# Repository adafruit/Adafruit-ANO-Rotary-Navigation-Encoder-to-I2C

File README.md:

## Adafruit ANO Rotary Navigation Encoder to I2C Stemma QT Adapter PCB

<a href="http://www.adafruit.com/products/5740"><br/>
Click here to purchase one from the Adafruit shop</a>

PCB files for the Adafruit ANO Rotary Navigation Encoder to I2C Stemma QT Adapter. 

Format is EagleCAD schematic and board layout
* https://www.adafruit.com/product/5740

### Description

The ANO rotary encoder wheel is a funky user interface element, reminiscent of the original clicking scroll wheel interface on the first iPods. It's a nifty kit, but the pin-out is a little odd - and there's a ton of pins needed to connect to the rotary encoder and 5 button switches.

This Stemma QT breakout makes all that frustration go away - solder in the ANO Directional Navigation and Scroll Wheel Rotary Encoder (not included). The onboard microcontroller is programmed with our seesaw firmware and will track all pulses and pins for you and then save the incremental value for querying at any time over I2C. Plug it in with a Stemma QT cable for instant rotary goodness, with any kind of microcontroller from an Arduino UNO up to a Raspberry Pi to one of our QT Py's.

You can use our Arduino library to control and read data with any compatible microcontroller. We also have CircuitPython/Python code for use with computers or single-board Linux boards.

Power with 3 to 5V DC, and then use 3 or 5V logic I2C data. The INT pin can be configured to pulse low whenever rotation or push-buttoning is detected so you do not have to spam-read the I2C port to detect motion. It's also easy to add this breakout to a breadboard - with six 0.1"-spaced breakout pads - if you so choose.

Four solder jumpers can be used to change the I2C address - up to 16 can share one I2C bus! If you happen to need more, it's possible to set the I2C address with a special address-change command that is saved to the onboard non-volatile EEPROM memory.

This is just the assembled and programmed 'seesaw' PCB for the ANO encoder, the encoder is NOT included! Pick one up here. Some soldering is required to attach the encoder to the backing.

### License

Adafruit invests time and resources providing this open source design, please support Adafruit and open-source hardware by purchasing products from [Adafruit](https://www.adafruit.com)!

Designed by Limor Fried/Ladyada for Adafruit Industries.

Creative Commons Attribution/Share-Alike, all text above must be included in any redistribution. 
See license.txt for additional details.

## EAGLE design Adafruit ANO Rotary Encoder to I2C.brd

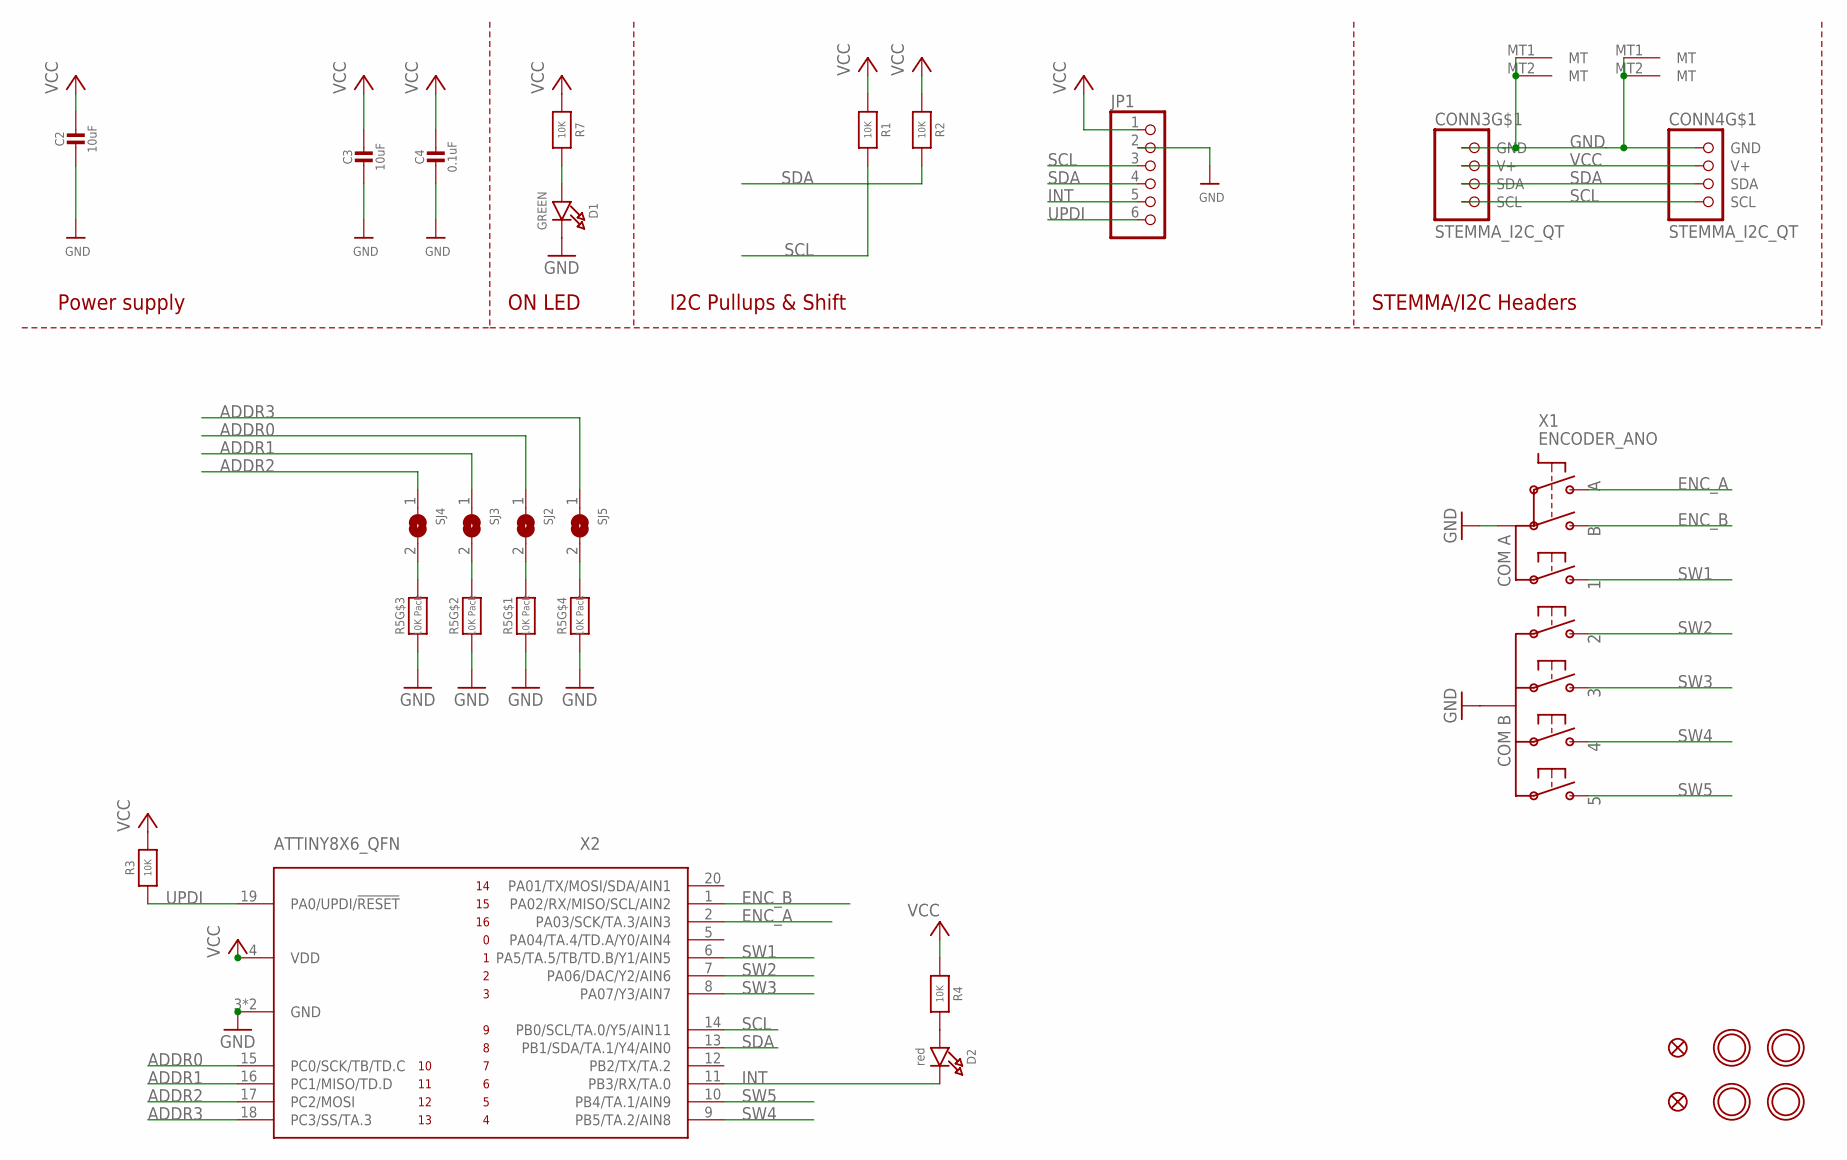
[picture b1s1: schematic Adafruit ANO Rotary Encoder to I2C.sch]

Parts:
C2, C3: 10uF; 0805-NO
C4: 0.1uF; 0603-NO
CONN3, CONN4: STEMMA_I2C_QT; JST_SH4
D1: GREEN; CHIPLED_0603_NOOUTLINE
D2: red; CHIPLED_0603_NOOUTLINE
FID3, FID4: FIDUCIAL_1MM
JP1: HEADER-1X670MIL; 1X06_ROUND_70
R1, R2, R3, R4, R7: 10K; 0603-NO
R5: 10K Pack; RESPACK_4X0603
SJ2, SJ3, SJ4, SJ5: SOLDERJUMPERCLOSED; SOLDERJUMPER_CLOSEDWIRE
U$25, U$27, U$29, U$30: MOUNTINGHOLE2.5; MOUNTINGHOLE_2.5_PLATED
X1: ENCODER_ANO
X2: ATTINY8X6_QFN; QFN20_3MM

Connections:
ADDR0: SJ2.1, X2.15 (PC0/SCK/TB/TD.C)
ADDR1: SJ3.1, X2.16 (PC1/MISO/TD.D)
ADDR2: SJ4.1, X2.17 (PC2/MOSI)
ADDR3: SJ5.1, X2.18 (PC3/SS/TA.3)
ENC_A: X1.A, X2.2 (PA03/SCK/TA.3/AIN3)
ENC_B: X1.B, X2.1 (PA02/RX/MISO/SCL/AIN2)
GND: C2.2, C3.2, C4.2, CONN3.1 (GND), CONN3.MT1 (MT), CONN3.MT2 (MT), CONN4.1 (GND), CONN4.MT1 (MT), CONN4.MT2 (MT), D1.C, JP1.2, R5.1, R5.2 (1), R5.3 (1), R5.4 (1), X1.COM_A (COMA), X1.COM_B, X2.3 (GND), X2.PAD (GND)
INT: D2.C, JP1.5, X2.11 (PB3/RX/TA.0)
unnamed: D1.A, R7.2
unnamed: D2.A, R4.2
unnamed: R5.8 (2), SJ2.2
unnamed: R5.7 (2), SJ3.2
unnamed: R5.6 (2), SJ4.2
unnamed: R5.5 (2), SJ5.2
SCL: CONN3.4 (SCL), CONN4.4 (SCL), JP1.3, R1.2, X2.14 (PB0/SCL/TA.0/Y5/AIN11)
SDA: CONN3.3 (SDA), CONN4.3 (SDA), JP1.4, R2.2, X2.13 (PB1/SDA/TA.1/Y4/AIN0)
SW1: X1.S1 (1), X2.6 (PA5/TA.5/TB/TD.B/Y1/AIN5)
SW2: X1.S2, X2.7 (PA06/DAC/Y2/AIN6)
SW3: X1.S3, X2.8 (PA07/Y3/AIN7)
SW4: X1.S4, X2.9 (PB5/TA.2/AIN8)
SW5: X1.S5, X2.10 (PB4/TA.1/AIN9)
UPDI: JP1.6, R3.1, X2.19 (PA0/UPDI/!RESET)
VCC: C2.1, C3.1, C4.1, CONN3.2 (V+), CONN4.2 (V+), JP1.1, R1.1, R2.1, R3.2, R4.1, R7.1, X2.4 (VDD)

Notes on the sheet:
I2C Pullups & Shift
STEMMA/I2C Headers
ON LED
Power supply

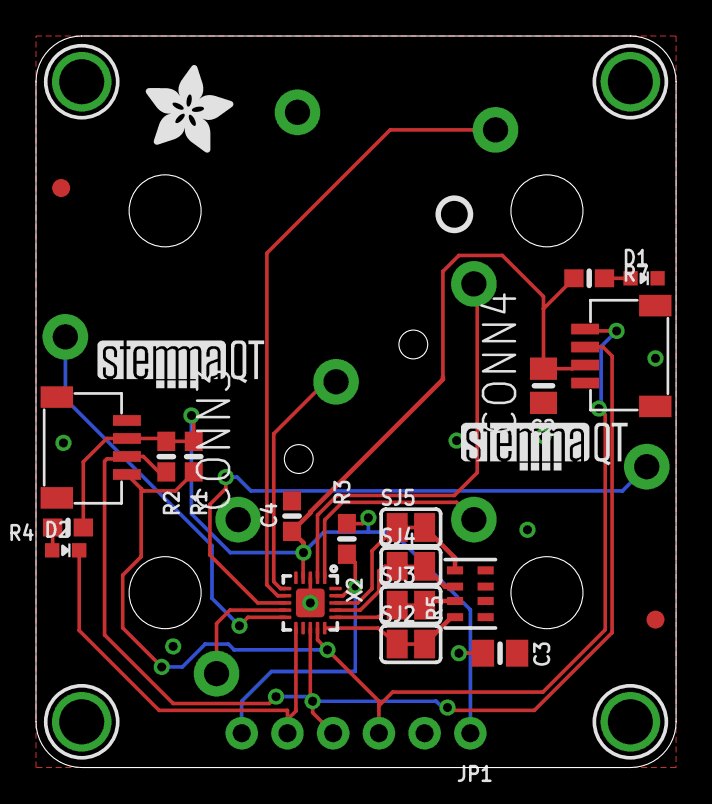
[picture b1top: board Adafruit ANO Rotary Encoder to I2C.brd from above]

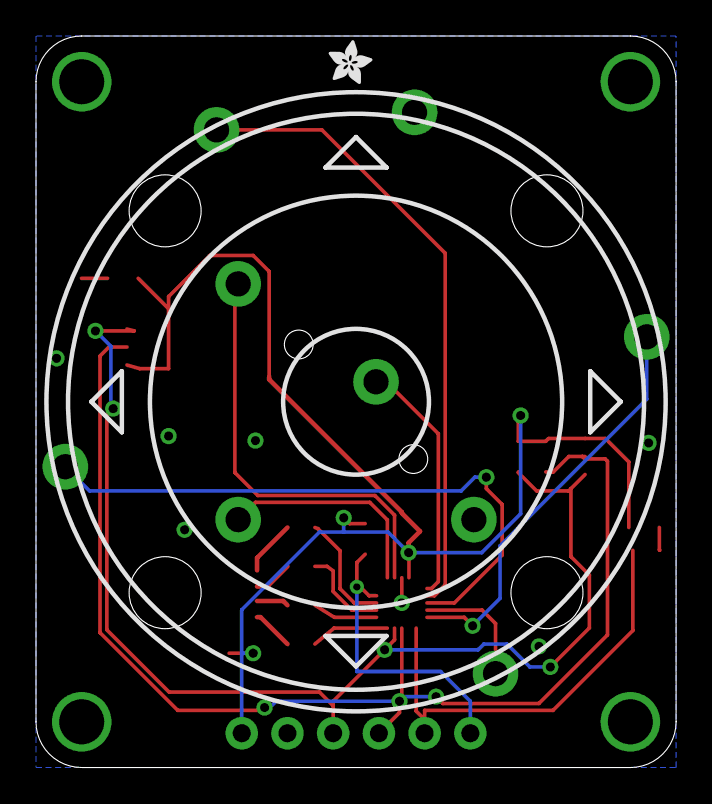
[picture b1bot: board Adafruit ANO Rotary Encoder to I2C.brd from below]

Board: 2 copper layers, 35.6 x 40.6 mm, 43 parts (2 on the bottom side), 23 nets.

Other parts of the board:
E$2: ADAFRUIT_2.5MM
PLABEL0: PLABEL0
PLABEL1: PLABEL1
PLABEL2: PLABEL2
PLABEL3: PLABEL3
PLABEL4: PLABEL4
PLABEL5: PLABEL5
PLABEL6: PLABEL6
PLABEL7: PLABEL7
PLABEL8: PLABEL8
PLABEL9: PLABEL9
PLABEL10: PLABEL10
PLABEL11: PLABEL11
U$2: ADAFRUIT_5MM
U$33: PCBFEAT-REV-040
U$34, U$35: STEMMAQT

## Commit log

2023-05-17 cookiecutter output

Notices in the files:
parts and their libraries:
microbuilder: This work is placed in the public domain, and may be freely used for commercial and non-commercial work with the following conditions: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
